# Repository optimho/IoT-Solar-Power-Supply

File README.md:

# IoT-Solar-Power-Supply
A small but highly efficient Solar power supply for electronics 

The repo consists of eagle cad files and a zip file with fabrication ready gerber files.

The power supply will charge a Lithium Ion 18650 battery and supply up to 4.1-3.0v 1A.
The battery voltage is monitored so that it will not run the battery flat and protect the battery. 

There is no short circuit protection on the device, so consider a 5v 1.5A fuse if you think that it is necssary.

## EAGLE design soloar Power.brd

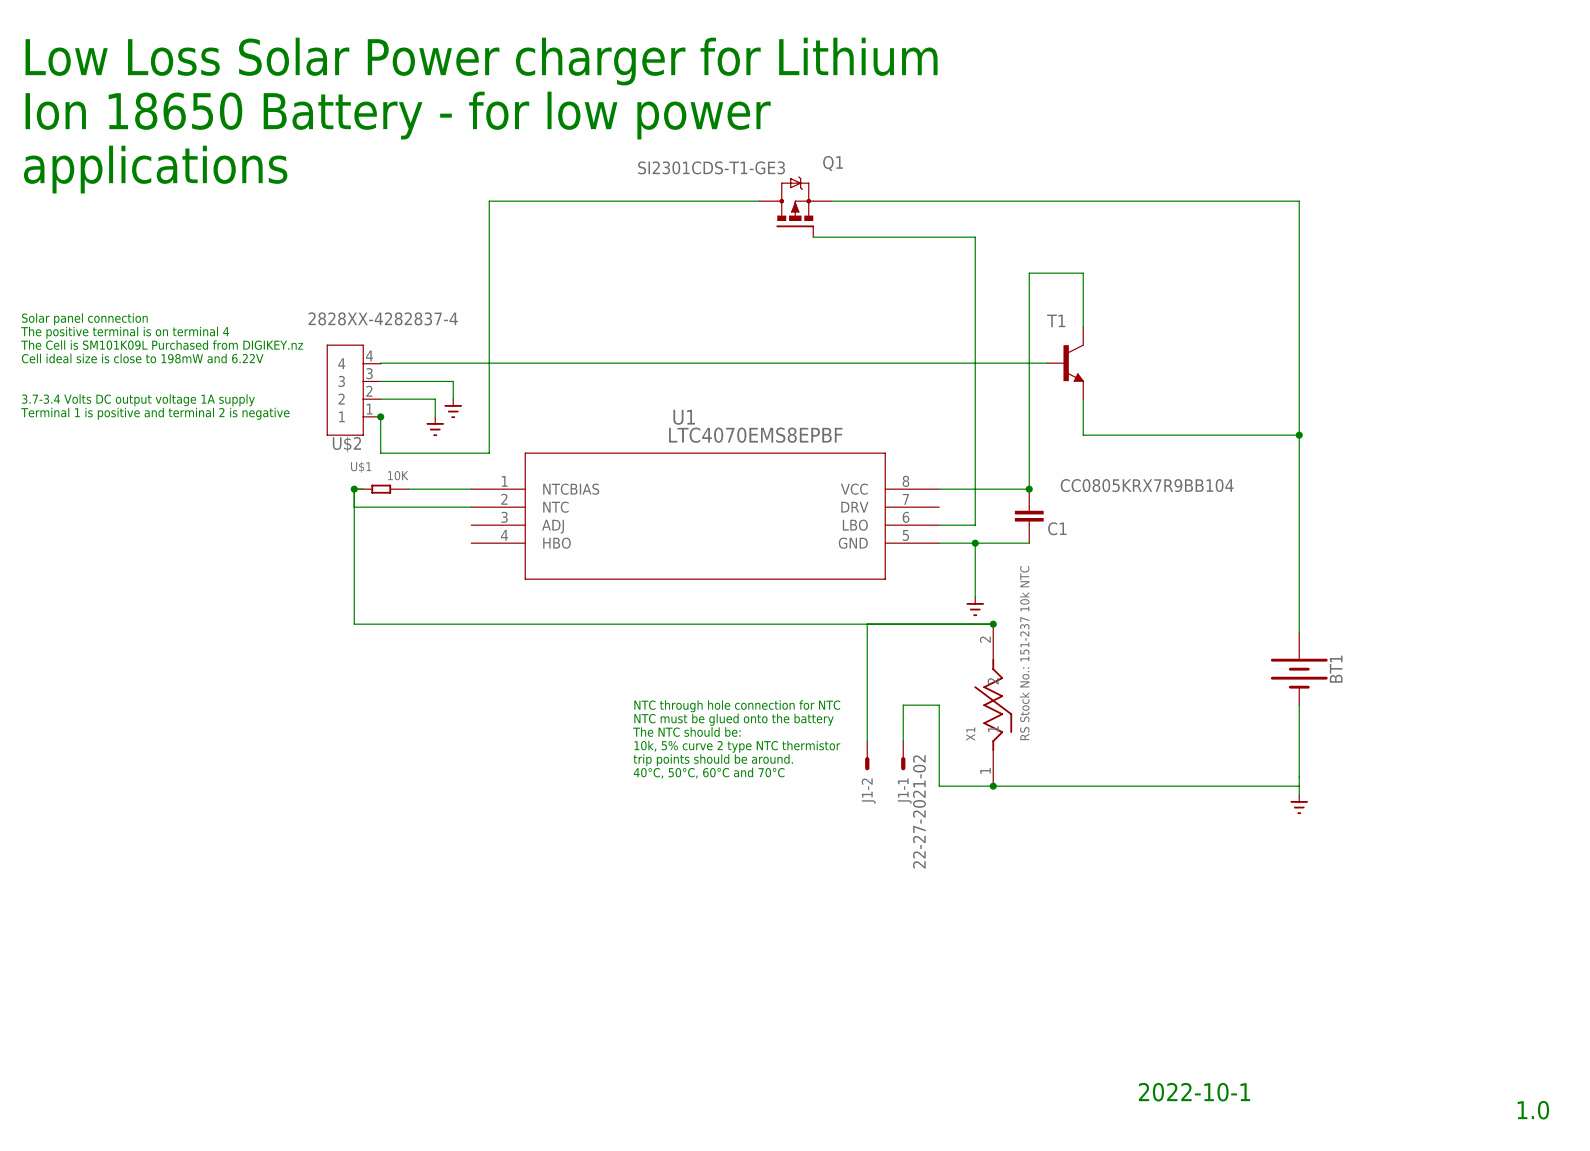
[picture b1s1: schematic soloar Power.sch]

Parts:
BT1: BATTERY-18650; BATTERY_18650-HOLDER
C1: CC0805KRX7R9BB104; CAP_0805
J1: 22-27-2021-02; 6410-02
Q1: SI2301CDS-T1-GE3; SOT23
T1: MMBT3904LT1-NPN-SOT23-BEC; SOT23-BEC
U1: LTC4070EMS8EPBF; MSOP-8_MS
U$1: 10K; R0805
U$2: 2828XX-4282837-4; TERMBLK_508-4N
X1: RS Stock No.: 151-237 10k NTC; NCP18WF104J03RB

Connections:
GND: BT1.GND@1 (-), C1.2, J1.1, U1.5 (GND), U$2.2, U$2.3, X1.1
unnamed: T1.B, U$2.4
unnamed: BT1.PWR@1 (+), Q1.2 (S), T1.E
unnamed: C1.1, T1.C, U1.8 (VCC)
unnamed: U1.1 (NTCBIAS), U$1.1
unnamed: Q1.3 (D), U$2.1
unnamed: J1.2, U1.2 (NTC), U$1.2, X1.2
unnamed: Q1.1 (G), U1.6 (LBO)

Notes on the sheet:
3.7-3.4 Volts DC output voltage 1A supply Terminal 1 is positive and terminal 2 is negative
Solar panel connection The positive terminal is on terminal 4 The Cell is SM101K09L Purchased from DIGIKEY.nz Cell ideal size is close to 198mW and 6.22V
NTC through hole connection for NTC NTC must be glued onto the battery The NTC should be: 10k, 5% curve 2 type NTC thermistor trip points should be around. 40°C, 50°C, 60°C and 70°C
Low Loss Solar Power charger for Lithium Ion 18650 Battery - for low power applications
2022-10-1
1.0

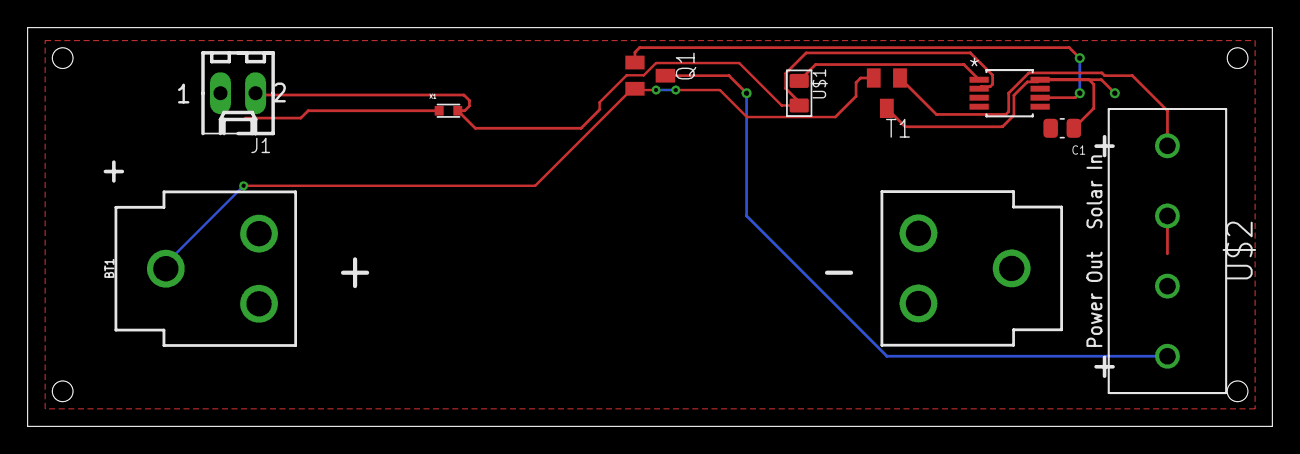
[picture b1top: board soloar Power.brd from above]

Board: 2 copper layers, 90.2 x 28.9 mm, 9 parts (0 on the bottom side), 8 nets.

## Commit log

2022-09-11 Initial commit of solar power source for IOT
2022-09-11 Create README.md
    Add some explanation text
2022-09-11 Add BOM

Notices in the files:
parts and their libraries:
SparkFun-Batteries: Licensing: Creative Commons ShareAlike 4.0 International - https://creativecommons.org/licenses/by-sa/4.0
